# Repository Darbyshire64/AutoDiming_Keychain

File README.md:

# AutoDiming_Keychain
An Auto Diming Keychain Themed Like a cat made outof  a pcb

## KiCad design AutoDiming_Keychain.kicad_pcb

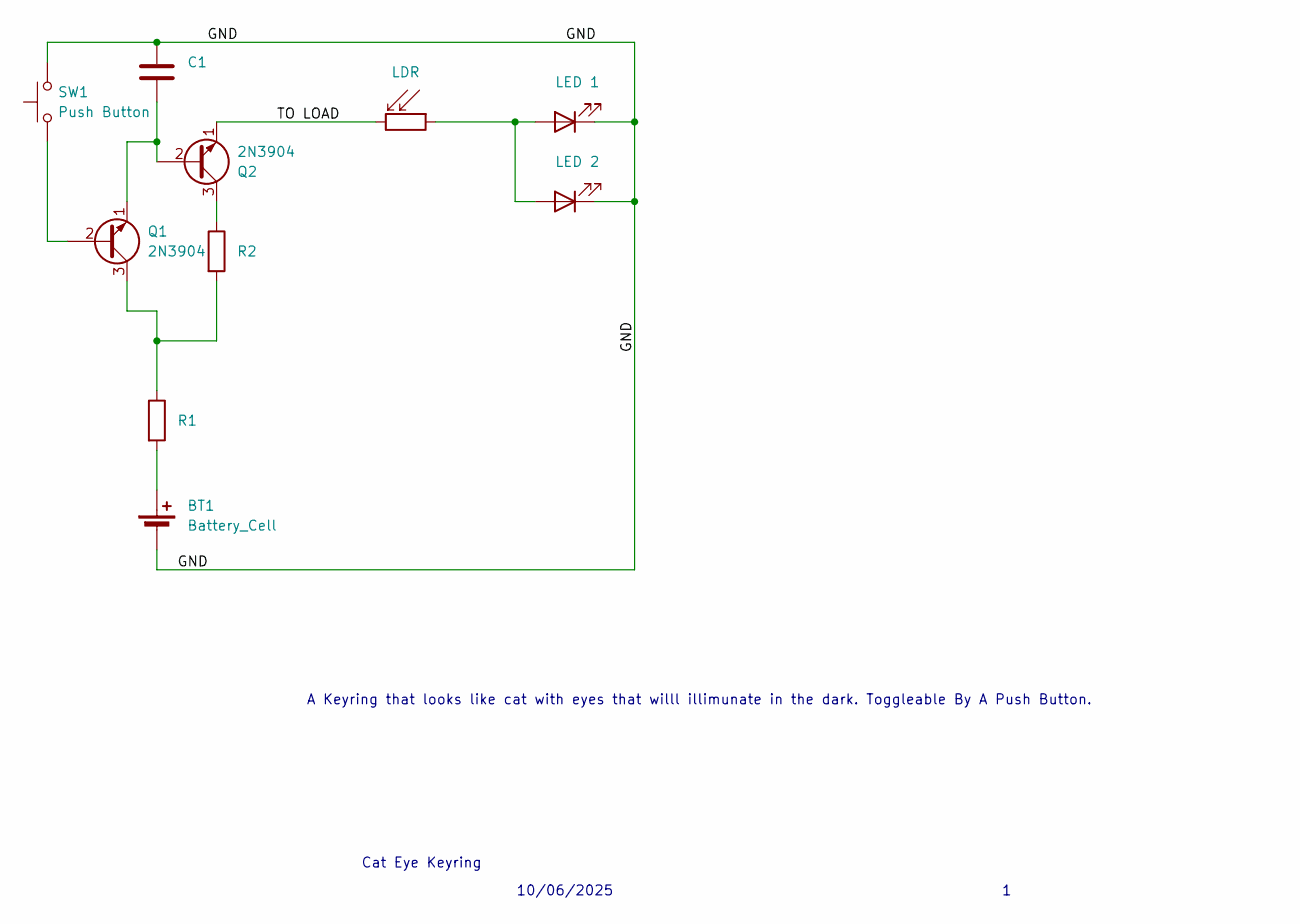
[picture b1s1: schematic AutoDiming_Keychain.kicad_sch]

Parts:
BT1: Battery_Cell; BatteryHolder_Keystone_3034_1x20mm
C1: C; CP_Radial_D8.0mm_P5.00mm
D1: LED 1; LED_D5.0mm
D2: LED 2; LED_D5.0mm
Q1, Q2: 2N3904; TO-92_Inline
R1: LDR; R_LDR_5.1x4.3mm_P3.4mm_Vertical
R2: R; R_Axial_DIN0207_L6.3mm_D2.5mm_P7.62mm_Horizontal
R3: R1; R_Axial_DIN0207_L6.3mm_D2.5mm_P7.62mm_Horizontal
SW1: Push Button; SW_PUSH_6mm

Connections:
/GND: BT1.2 (-), C1.1, D1.1 (K), D2.1 (K), SW1.2
/TO LOAD: Q2.1 (E), R1.2
unnamed: BT1.1 (+), R3.2
unnamed: D1.2 (A), D2.2 (A), R1.1
unnamed: Q1.2 (B), SW1.1
unnamed: Q1.3 (C), R2.2, R3.1
unnamed: C1.2, Q1.1 (E), Q2.2 (B)
unnamed: Q2.3 (C), R2.1

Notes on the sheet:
Cat Eye Keyring
10/06/2025
A Keyring that looks like cat with eyes that willl illimunate in the dark. Toggleable By A Push Button.

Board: 2 copper layers, 10 parts (4 on the bottom side), 8 nets, no tracks yet.
